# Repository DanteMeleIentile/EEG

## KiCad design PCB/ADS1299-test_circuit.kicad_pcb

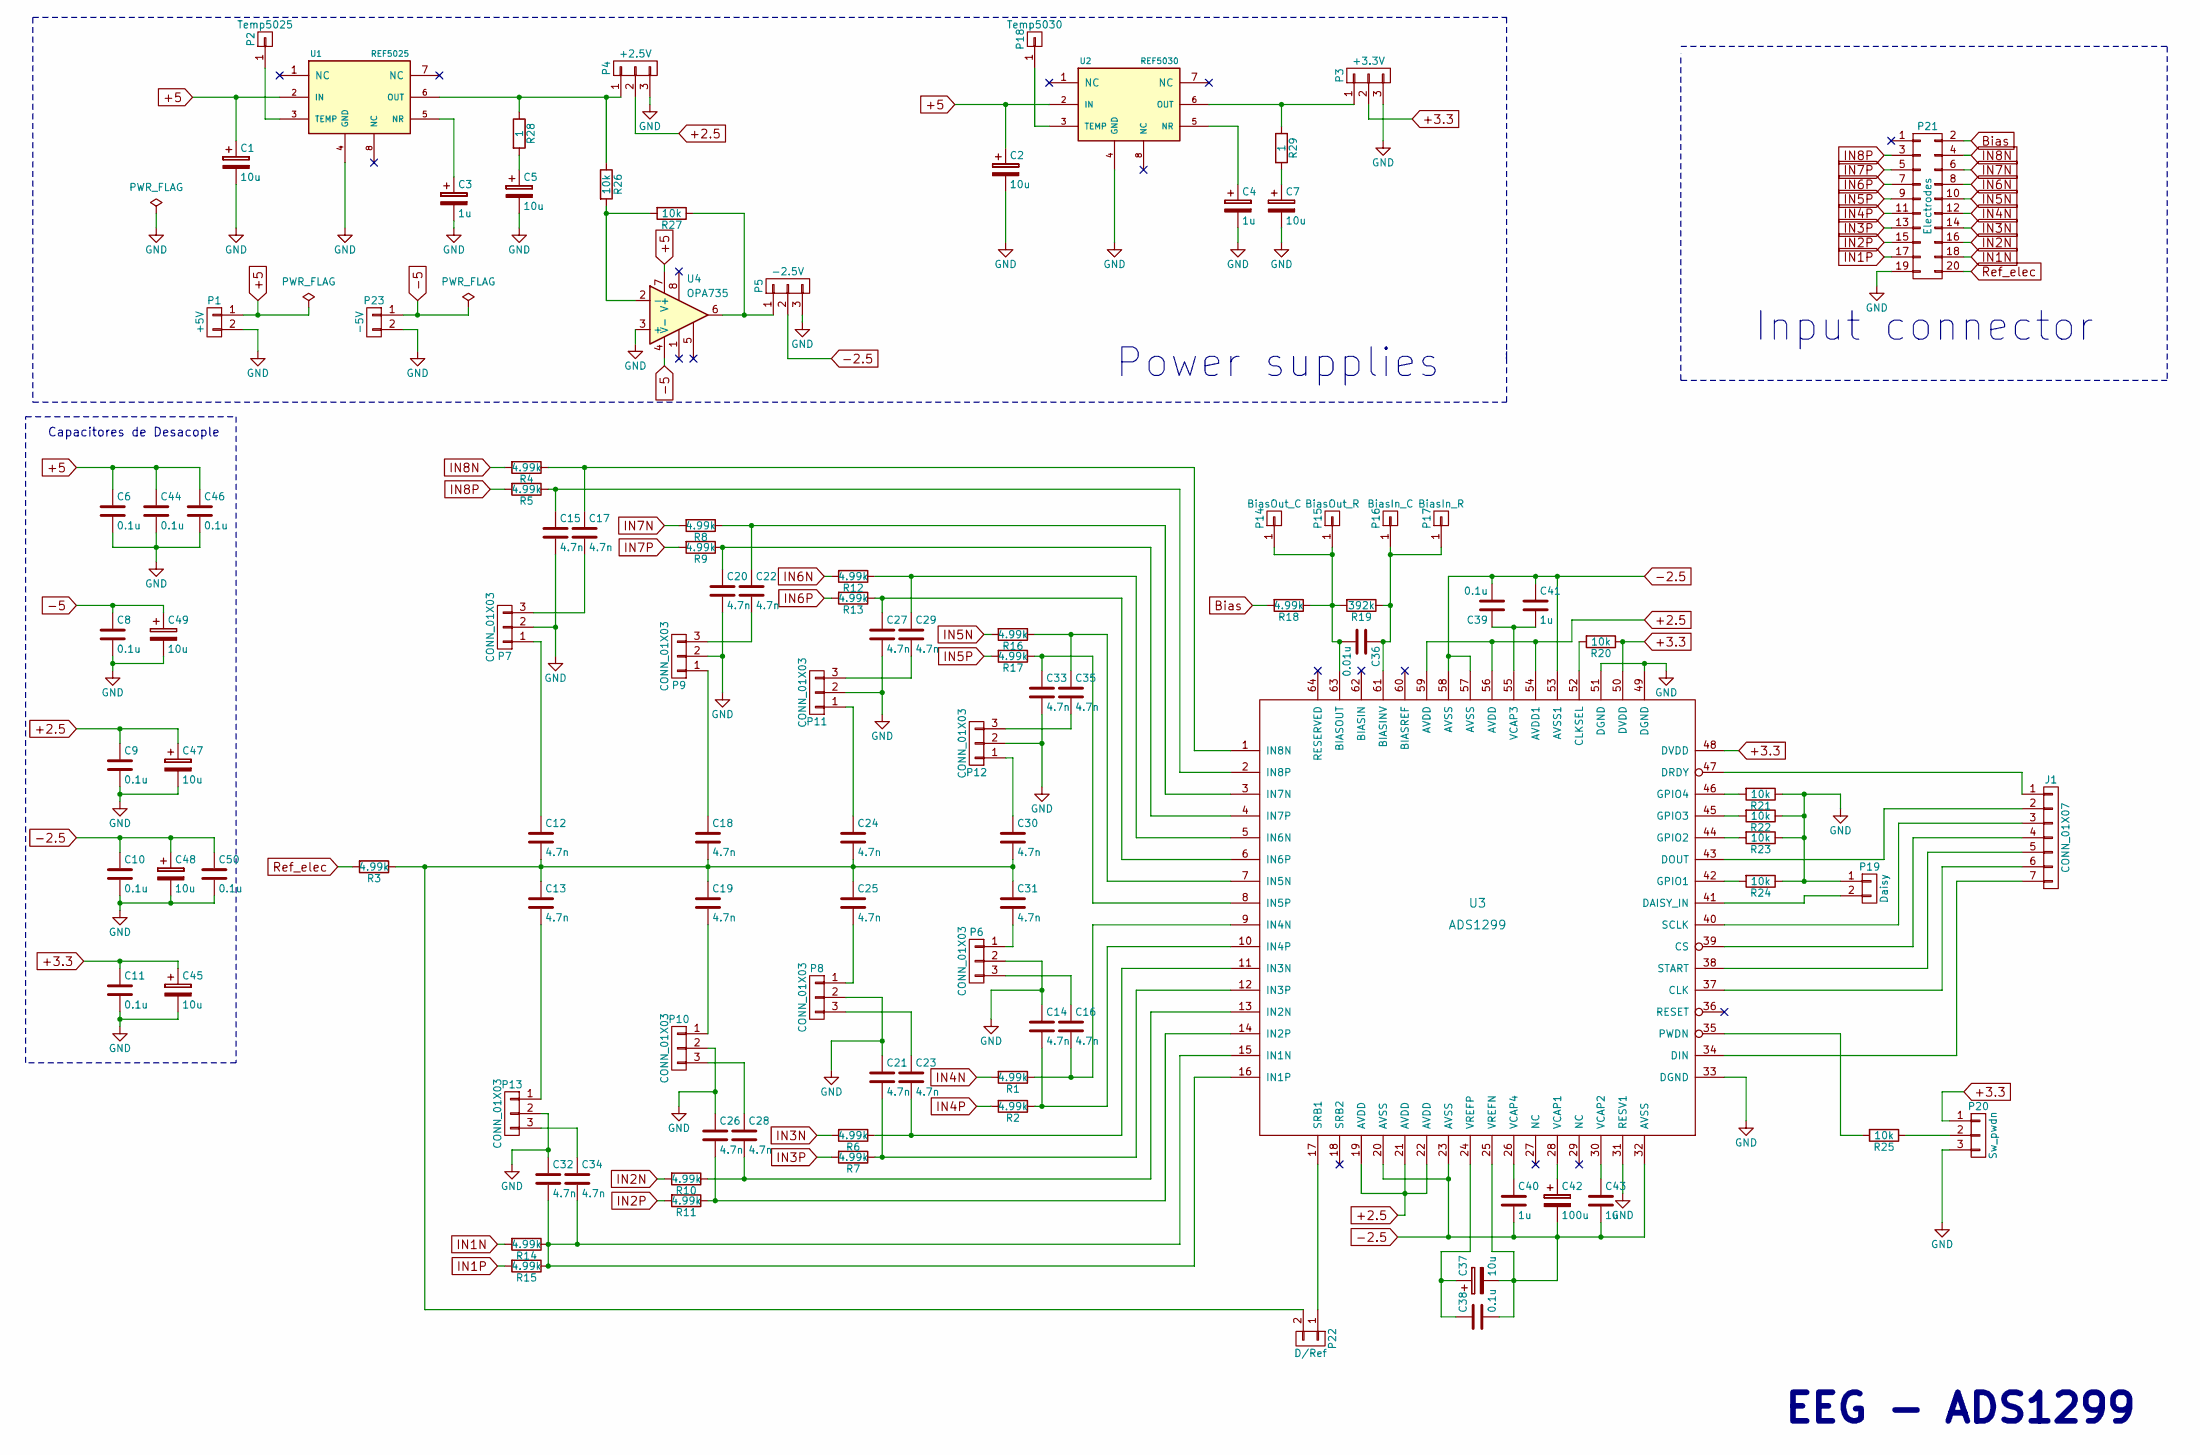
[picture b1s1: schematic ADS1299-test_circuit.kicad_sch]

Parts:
C1, C2, C5, C7, C45, C47, C48, C49: 10u; CP_Elec_6.3x5.8
C3, C4: 1u; CP_Elec_4x4.5
C6, C8, C9, C10, C11, C38, C39, C44, C46, C50: 0.1u; C_0805
C12, C13, C18, C19, C24, C25, C30, C31: 4.7n; C_0805
C14, C15, C16, C17, C20, C21, C22, C23, C26, C27, C28, C29, C32, C33, C34, C35: 4.7n; C_1206
C36: 0.01u; C_0805
C37: 10u; C_1206
C40, C43: 1u; C_0805
C41: 1u; C_1206
C42: 100u; C_1206
J1: CONN_01X07; Pin_Header_Straight_1x07_Pitch2.54mm
P1: +5V; Pin_Header_Straight_1x02_Pitch2.54mm
P2: Temp5025; Pin_Header_Straight_1x01_Pitch1.27mm
P3: +3.3V; Pin_Header_Straight_1x03_Pitch2.54mm
P4: +2.5V; Pin_Header_Straight_1x03_Pitch2.54mm
P5: -2.5V; Pin_Header_Straight_1x03_Pitch2.54mm
P6, P7, P8, P9, P10, P11, P12, P13: CONN_01X03; Pin_Header_Straight_1x03_Pitch2.54mm
P14: BiasOut_C; Pin_Header_Straight_1x01_Pitch2.54mm
P15: BiasOut_R; Pin_Header_Straight_1x01_Pitch2.54mm
P16: BiasIn_C; Pin_Header_Straight_1x01_Pitch2.54mm
P17: BiasIn_R; Pin_Header_Straight_1x01_Pitch2.54mm
P18: Temp5030; Pin_Header_Straight_1x01_Pitch1.27mm
P19: Daisy; Pin_Header_Straight_1x02_Pitch2.54mm
P20: Sw_pwdn; Pin_Header_Straight_1x03_Pitch2.54mm
P21: Electrodes; Pin_Header_Straight_2x10_Pitch2.54mm_Mirrored
P22: D/Ref; Pin_Header_Straight_1x02_Pitch2.54mm
P23: -5V; Pin_Header_Straight_1x02_Pitch2.54mm
R1, R2, R3, R4, R5, R6, R7, R8, R9, R10, R11, R12, R13, R14, R15, R16, R17, R18: 4.99k; R_0805
R19: 392k; R_0805
R20, R26, R27: 10k; R_0805
R21, R22, R23, R24, R25: 10k; R_1206
R28, R29: 1; R_0805
U1: REF5025; SOIC-8_3.9x4.9mm_Pitch1.27mm
U2: REF5030; SOIC-8_3.9x4.9mm_Pitch1.27mm
U3: ADS1299; LQFP-64_10x10mm_Pitch0.5mm
U4: OPA735; SOIC-8_3.9x4.9mm_Pitch1.27mm

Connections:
+2.5: C9.1, C47.1, P4.2, U3.19 (AVDD), U3.21 (AVDD), U3.22 (AVDD), U3.54 (AVDD1), U3.56 (AVDD), U3.59 (AVDD)
+3.3: C11.1, C45.1, P3.2, P20.1, R20.1, U3.48 (DVDD), U3.50 (DVDD)
+5: C1.1, C2.1, C6.1, C44.1, C46.1, P1.1, U1.2 (IN), U2.2 (IN), U4.7 (V+)
-2.5: C10.1, C37.2, C38.2, C39.2, C40.2, C41.1, C42.2, C43.2, C48.1, C50.1, P5.2, U3.20 (AVSS), U3.23 (AVSS), U3.25 (VREFN), U3.32 (AVSS), U3.53 (AVSS1), U3.57 (AVSS), U3.58 (AVSS)
-5: C8.1, C49.1, P23.1, U4.4 (V-)
Bias: P21.2, R18.2
GND: C1.2, C2.2, C3.2, C4.2, C5.2, C6.2, C7.2, C8.2, C9.2, C10.2, C11.2, C14.1, C15.2, C20.2, C21.1, C26.1, C27.2, C32.1, C33.2, C44.2, C45.2, C46.2, C47.2, C48.2, C49.2, C50.2, P1.2, P3.3, P4.3, P5.3, P6.2, P7.2, P8.2, P9.2, P10.2, P11.2, P12.2, P13.2, P19.1, P20.3, P21.19, P23.2, R21.1, R22.1, R23.1, R24.1, U1.4 (GND), U2.4 (GND), U3.31 (RESV1), U3.33 (DGND), U3.49 (DGND), U3.51 (DGND), U4.3 (+)
IN1N: P21.18, R14.2
IN1P: P21.17, R15.2
IN2N: P21.16, R10.2
IN2P: P21.15, R11.2
IN3N: P21.14, R6.2
IN3P: P21.13, R7.2
IN4N: P21.12, R1.2
IN4P: P21.11, R2.2
IN5N: P21.10, R16.2
IN5P: P21.9, R17.2
IN6N: P21.8, R12.2
IN6P: P21.7, R13.2
IN7N: P21.6, R8.2
IN7P: P21.5, R9.2
IN8N: P21.4, R4.2
IN8P: P21.3, R5.2
unnamed: C3.1, U1.5 (NR)
unnamed: C4.1, U2.5 (NR)
unnamed: C5.1, R28.2
unnamed: C7.1, R29.2
unnamed: C12.1, P7.1
unnamed: C12.2, C13.1, C18.2, C19.1, C24.2, C25.1, C30.2, C31.1, P22.2, R3.1
unnamed: C13.2, P13.1
unnamed: C14.2, R2.1, U3.10 (IN4P)
unnamed: C15.1, R5.1, U3.2 (IN8P)
unnamed: C16.1, P6.3
unnamed: C16.2, R1.1, U3.9 (IN4N)
unnamed: C17.1, R4.1, U3.1 (IN8N)
unnamed: C17.2, P7.3
unnamed: C18.1, P9.1
unnamed: C19.2, P10.1
unnamed: C20.1, R9.1, U3.4 (IN7P)
unnamed: C21.2, R7.1, U3.12 (IN3P)
unnamed: C22.1, R8.1, U3.3 (IN7N)
unnamed: C22.2, P9.3
unnamed: C23.1, P8.3
unnamed: C23.2, R6.1, U3.11 (IN3N)
unnamed: C24.1, P11.1
unnamed: C25.2, P8.1
unnamed: C26.2, R11.1, U3.14 (IN2P)
unnamed: C27.1, R13.1, U3.6 (IN6P)
unnamed: C28.1, P10.3
unnamed: C28.2, R10.1, U3.13 (IN2N)
unnamed: C29.1, R12.1, U3.5 (IN6N)
unnamed: C29.2, P11.3
unnamed: C30.1, P12.1
unnamed: C31.2, P6.1
unnamed: C33.1, R17.1, U3.8 (IN5P)
unnamed: C34.1, P13.3
unnamed: C35.1, R16.1, U3.7 (IN5N)
unnamed: C35.2, P12.3
unnamed: C36.1, P16.1, P17.1, R19.1, U3.61 (BIASINV)
unnamed: C36.2, P14.1, P15.1, R18.1, R19.2, U3.63 (BIASOUT)
unnamed: C37.1, C38.1, U3.24 (VREFP)
unnamed: C39.1, C41.2, U3.55 (VCAP3)
unnamed: C40.1, U3.26 (VCAP4)
unnamed: C42.1, U3.28 (VCAP1)
unnamed: C43.1, U3.30 (VCAP2)
unnamed: J1.1, U3.47 (DRDY)
unnamed: J1.2, U3.43 (DOUT)
unnamed: J1.3, U3.40 (SCLK)
unnamed: J1.4, U3.39 (CS)
unnamed: J1.5, U3.38 (START)
unnamed: J1.6, U3.37 (CLK)
unnamed: J1.7, U3.34 (DIN)
unnamed: P2.1, U1.3 (TEMP)
unnamed: P3.1, R29.1, U2.6 (OUT)
unnamed: P4.1, R26.1, R28.1, U1.6 (OUT)
unnamed: P5.1, R27.1, U4.6
unnamed: P18.1, U2.3 (TEMP)
unnamed: P19.2, U3.41 (DAISY_IN)
unnamed: P20.2, R25.1
unnamed: P22.1, U3.17 (SRB1)
unnamed: R20.2, U3.52 (CLKSEL)
unnamed: R21.2, U3.46 (GPIO4)
unnamed: R22.2, U3.45 (GPIO3)
unnamed: R23.2, U3.44 (GPIO2)
unnamed: R24.2, U3.42 (GPIO1)
unnamed: R25.2, U3.35 (PWDN)
unnamed: R26.2, R27.2, U4.2 (-)
Ref_elec: P21.20, R3.2

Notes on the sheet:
EEG - ADS1299
Input connector
Capacitores de Desacople
Power supplies

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
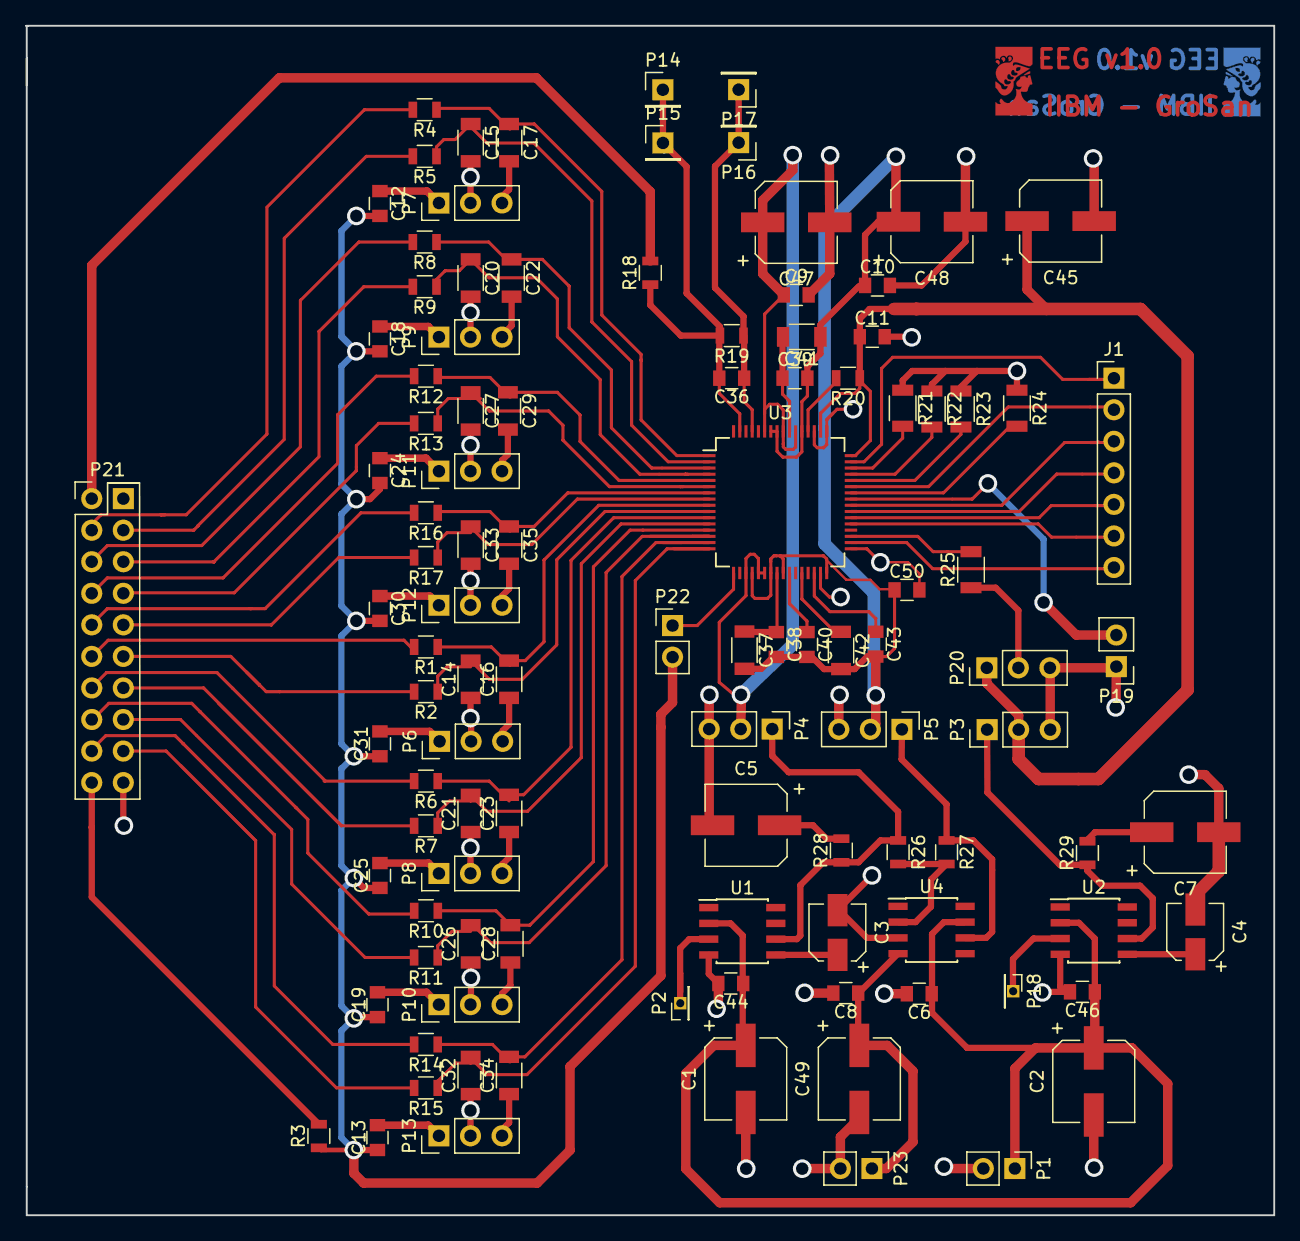
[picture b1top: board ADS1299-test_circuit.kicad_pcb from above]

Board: 2 copper layers, 100.5 x 95.8 mm, 107 parts (0 on the bottom side), 90 nets.

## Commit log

2026-06-26 recupero libs
2026-06-26 Funcionando para consutlas
